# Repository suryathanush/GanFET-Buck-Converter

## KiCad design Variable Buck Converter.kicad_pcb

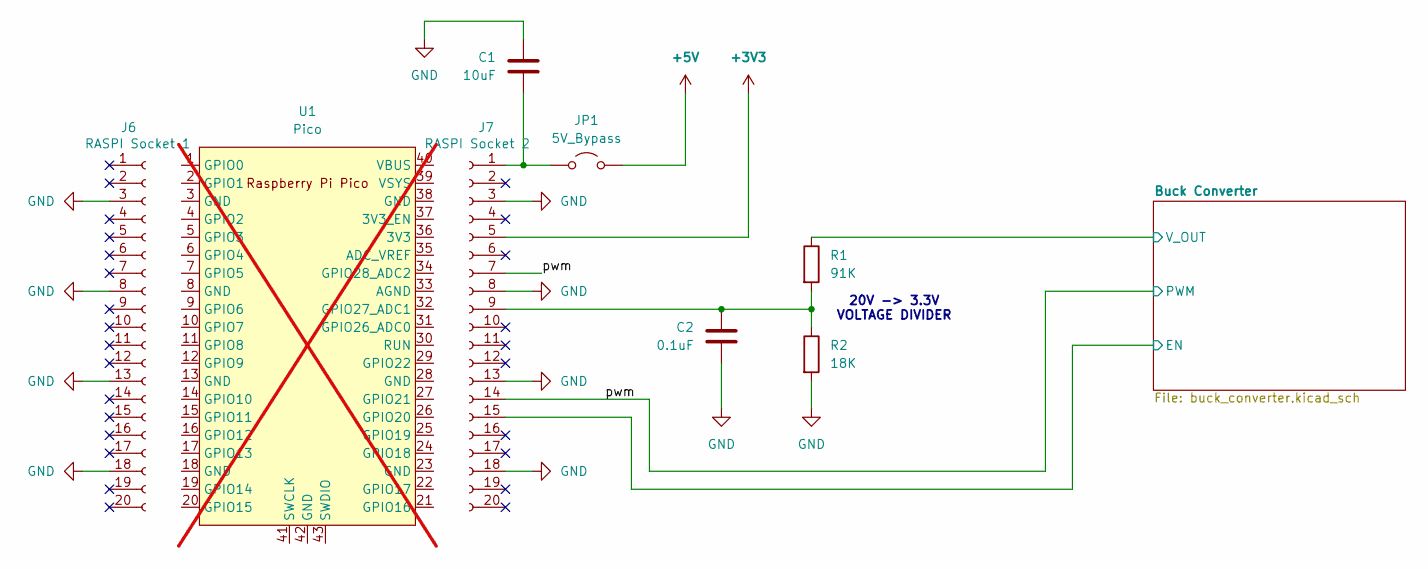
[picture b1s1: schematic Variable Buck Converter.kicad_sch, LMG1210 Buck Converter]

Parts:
C1: 10uF; C_0603_1608Metric; Manufacturer_Part_Number CL10A106MA8NRNC
C2: 0.1uF; C_0603_1608Metric; Manufacturer_Part_Number CL10B104JB8NNND
J6: RASPI Socket 1; PinSocket_1x20_P2.54mm_Vertical; Manufacturer_Part_Number PH1-20-UA
J7: RASPI Socket 2; PinSocket_1x20_P2.54mm_Vertical; Manufacturer_Part_Number PH1-20-UA
JP1: 5V_Bypass; PinHeader_1x02_P2.54mm_Vertical; Manufacturer_Part_Number HTSW-102-07-T-S
R1: 91K; R_0603_1608Metric; Manufacturer_Part_Number RT0603BRD0791KL
R2: 18K; R_0603_1608Metric; Manufacturer_Part_Number RT0603BRD0718KL
U1: Pico; RPi_Pico_SMD_TH; not fitted

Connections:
+3V3: J7.5; also elsewhere on the board
+5V: JP1.2 (B); also elsewhere on the board
/Buck Converter/EN: J7.15; also elsewhere on the board
/Buck Converter/V_OUT: R1.1; also elsewhere on the board
/pwm: J7.7, J7.14; also elsewhere on the board
GND: C1.1, C2.2, J6.3, J6.8, J6.13, J6.18, J7.3, J7.8, J7.13, J7.18, R2.2; also elsewhere on the board
unnamed: C1.2, J7.1, JP1.1 (A)
unnamed: C2.1, J7.9, R1.2, R2.1

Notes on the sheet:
20V -> 3.3V VOLTAGE DIVIDER

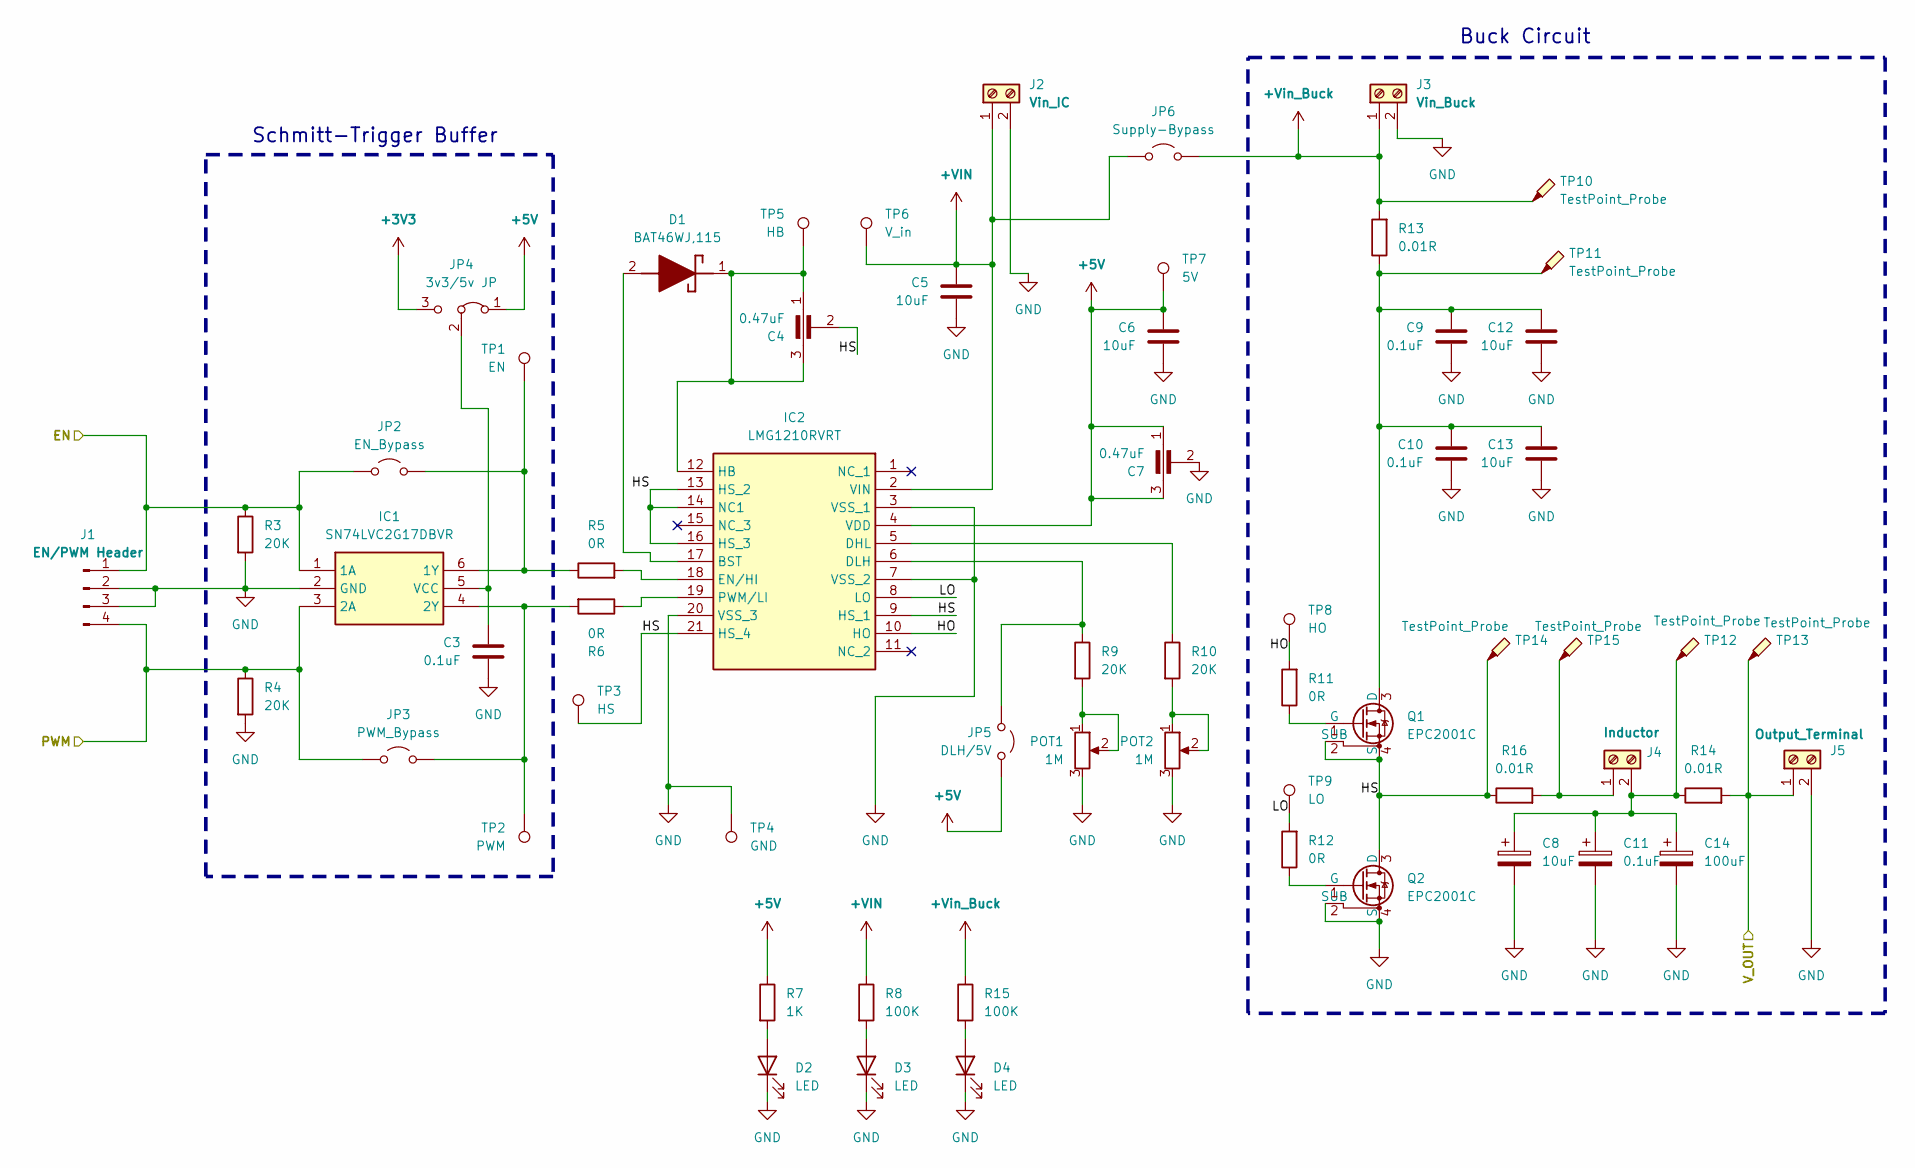
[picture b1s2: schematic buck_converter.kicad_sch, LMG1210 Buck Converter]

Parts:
C3, C9, C10, C11: 0.1uF; C_0603_1608Metric; Manufacturer_Part_Number CL10B104JB8NNND
C4, C7: 0.47uF; YFF18PW0J474MT0H0N; Manufacturer_Part_Number YFF18PW0J474MT0H0N
C5, C6, C8, C12, C13: 10uF; C_0603_1608Metric; Manufacturer_Part_Number CL10A106MA8NRNC
C14: 100uF; CP_Elec_6.3x5.9; Manufacturer_Part_Number 865080545012
D1: BAT46WJ,115; SODFL2512X80N; Manufacturer_Part_Number BAT46WJ,115; Mouser Part Number 771-BAT46WJ115
D2, D3, D4: LED; LED_0603_1608Metric; Manufacturer_Part_Number LTST-C190GKT
IC1: SN74LVC2G17DBVR; SOT95P280X145-6N; Manufacturer_Part_Number SN74LVC2G17DBVR; Mouser Part Number 595-SN74LVC2G17DBVR
IC2: LMG1210RVRT; Manufacturer_Part_Number LMG1210RVRT; Mouser Part Number 595-LMG1210RVRT
J1: EN/PWM Header; PinHeader_1x04_P2.54mm_Vertical; Manufacturer_Part_Number PH1-04-UA
J2: Vin_IC; TerminalBlock_Phoenix_MKDS-1,5-2_1x02_P5.00mm_Horizontal; Manufacturer_Part_Number 1548128
J3: Vin_Buck; TerminalBlock_Phoenix_MKDS-1,5-2_1x02_P5.00mm_Horizontal; Manufacturer_Part_Number 1548128
J4: Inductor; TerminalBlock_Phoenix_MKDS-1,5-2_1x02_P5.00mm_Horizontal; Manufacturer_Part_Number 1548128
J5: Output_Terminal; TerminalBlock_Phoenix_MKDS-1,5-2_1x02_P5.00mm_Horizontal; Manufacturer_Part_Number 1548128
JP2: EN_Bypass; PinHeader_1x02_P2.54mm_Vertical; Manufacturer_Part_Number HTSW-102-07-T-S
JP3: PWM_Bypass; PinHeader_1x02_P2.54mm_Vertical; Manufacturer_Part_Number HTSW-102-07-T-S
JP4: 3v3/5v JP; PinHeader_1x03_P2.54mm_Vertical; Manufacturer_Part_Number PH1-03-UA
JP5: DLH/5V; PinHeader_1x02_P2.54mm_Vertical; Manufacturer_Part_Number HTSW-102-07-T-S
JP6: Supply-Bypass; PinHeader_1x02_P2.54mm_Vertical; Manufacturer_Part_Number HTSW-102-07-T-S
POT1, POT2: 1M; Potentiometer_Bourns_3296W_Vertical; Manufacturer_Part_Number 3296W-1-105LF
Q1, Q2: EPC2001C; Manufacturer_Part_Number EPC2001C
R3, R4, R9, R10: 20K; R_0603_1608Metric; Manufacturer_Part_Number RT0603FRE0720KL
R5, R6, R11, R12: 0R; R_0603_1608Metric; Manufacturer_Part_Number RCG06030000Z0EA
R7: 1K; R_0603_1608Metric; Manufacturer_Part_Number RT0603FRE131KL
R8, R15: 100K; R_0603_1608Metric; Manufacturer_Part_Number RT0603FRE07100KL
R13, R14, R16: 0.01R; R_1206_3216Metric; Manufacturer_Part_Number PE1206DRM7W0R01L
TP1: EN; TestPoint_Loop_D2.60mm_Drill1.6mm_Beaded; Manufacturer_Part_Number 5278
TP2: PWM; TestPoint_Loop_D2.60mm_Drill1.6mm_Beaded; Manufacturer_Part_Number 5278
TP3: HS; TestPoint_Loop_D2.60mm_Drill1.6mm_Beaded; Manufacturer_Part_Number 5271
TP4: GND; TestPoint_Loop_D2.60mm_Drill1.6mm_Beaded; Manufacturer_Part_Number 5271
TP5: HB; TestPoint_Loop_D2.60mm_Drill1.6mm_Beaded; Manufacturer_Part_Number 5278
TP6: V_in; TestPoint_Loop_D2.60mm_Drill1.6mm_Beaded; Manufacturer_Part_Number 5270
TP7: 5V; TestPoint_Loop_D2.60mm_Drill1.6mm_Beaded; Manufacturer_Part_Number 5270
TP8: HO; TestPoint_Loop_D2.60mm_Drill1.6mm_Beaded; Manufacturer_Part_Number 5273
TP9: LO; TestPoint_Loop_D2.60mm_Drill1.6mm_Beaded; Manufacturer_Part_Number 5273
TP10, TP11: TestPoint_Probe; TestPoint_Loop_D2.60mm_Drill1.6mm_Beaded; Manufacturer_Part_Number 5270
TP12, TP13: TestPoint_Probe; TestPoint_Loop_D2.60mm_Drill1.6mm_Beaded; Manufacturer_Part_Number 5274
TP14, TP15: TestPoint_Probe; TestPoint_Loop_D2.60mm_Drill1.6mm_Beaded; Manufacturer_Part_Number 5277

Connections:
+3V3: JP4.3 (B); also elsewhere on the board
+5V: C6.1, C7.1, C7.3, IC2.4 (VDD), JP4.1 (A), JP5.1 (A), R7.1, TP7.1; also elsewhere on the board
+VIN: C5.1, IC2.2 (VIN), J2.1, JP6.1 (A), R8.1, TP6.1
+Vin_Buck: J3.1, JP6.2 (B), R13.2, R15.1, TP10.1
/Buck Converter/EN: IC1.1 (1A), J1.1, JP2.1 (A), R3.1; also elsewhere on the board
/Buck Converter/HO: IC2.10 (HO), R11.2, TP8.1
/Buck Converter/HS: C4.2, IC2.9 (HS_1), IC2.13 (HS_2), IC2.14 (NC1), IC2.16 (HS_3), IC2.21 (HS_4), Q1.2 (SUB), Q1.4 (S), Q1.6 (S), Q1.8 (S), Q1.10 (S), Q2.3 (D), Q2.5 (D), Q2.7 (D), Q2.9 (D), Q2.11 (D), R16.1, TP3.1, TP14.1
/Buck Converter/LO: IC2.8 (LO), R12.2, TP9.1
/Buck Converter/V_OUT: J5.1, R14.2, TP13.1; also elsewhere on the board
/pwm: IC1.3 (2A), J1.4, JP3.1 (A), R4.1; also elsewhere on the board
GND: C3.2, C5.2, C6.2, C7.2, C8.2, C9.2, C10.2, C11.2, C12.2, C13.2, C14.2, D2.1 (K), D3.1 (K), D4.1 (K), IC1.2 (GND), IC2.3 (VSS_1), IC2.7 (VSS_2), IC2.20 (VSS_3), J1.2, J1.3, J2.2, J3.2, J5.2, POT1.3, POT2.3, Q2.2 (SUB), Q2.4 (S), Q2.6 (S), Q2.8 (S), Q2.10 (S), R3.2, R4.2, TP4.1; also elsewhere on the board
unnamed: C9.1, C10.1, C12.1, C13.1, Q1.3 (D), Q1.5 (D), Q1.7 (D), Q1.9 (D), Q1.11 (D), R13.1, TP11.1
unnamed: D1.2 (A), IC2.17 (BST)
unnamed: C4.1, C4.3, D1.1 (K), IC2.12 (HB), TP5.1
unnamed: D2.2 (A), R7.2
unnamed: D3.2 (A), R8.2
unnamed: D4.2 (A), R15.2
unnamed: IC1.6 (1Y), JP2.2 (B), R5.1, TP1.1
unnamed: IC1.4 (2Y), JP3.2 (B), R6.2, TP2.1
unnamed: C3.1, IC1.5 (VCC), JP4.2 (C)
unnamed: IC2.5 (DHL), R10.1
unnamed: IC2.6 (DLH), JP5.2 (B), R9.1
unnamed: IC2.18 (EN/HI), R5.2
unnamed: IC2.19 (PWM/LI), R6.1
unnamed: J4.1, R16.2, TP15.1
unnamed: C8.1, C11.1, C14.1, J4.2, R14.1, TP12.1
unnamed: POT1.1, POT1.2, R9.2
unnamed: POT2.1, POT2.2, R10.2
unnamed: Q1.1 (G), R11.1
unnamed: Q2.1 (G), R12.1

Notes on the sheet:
Buck Circuit
Schmitt-Trigger Buffer

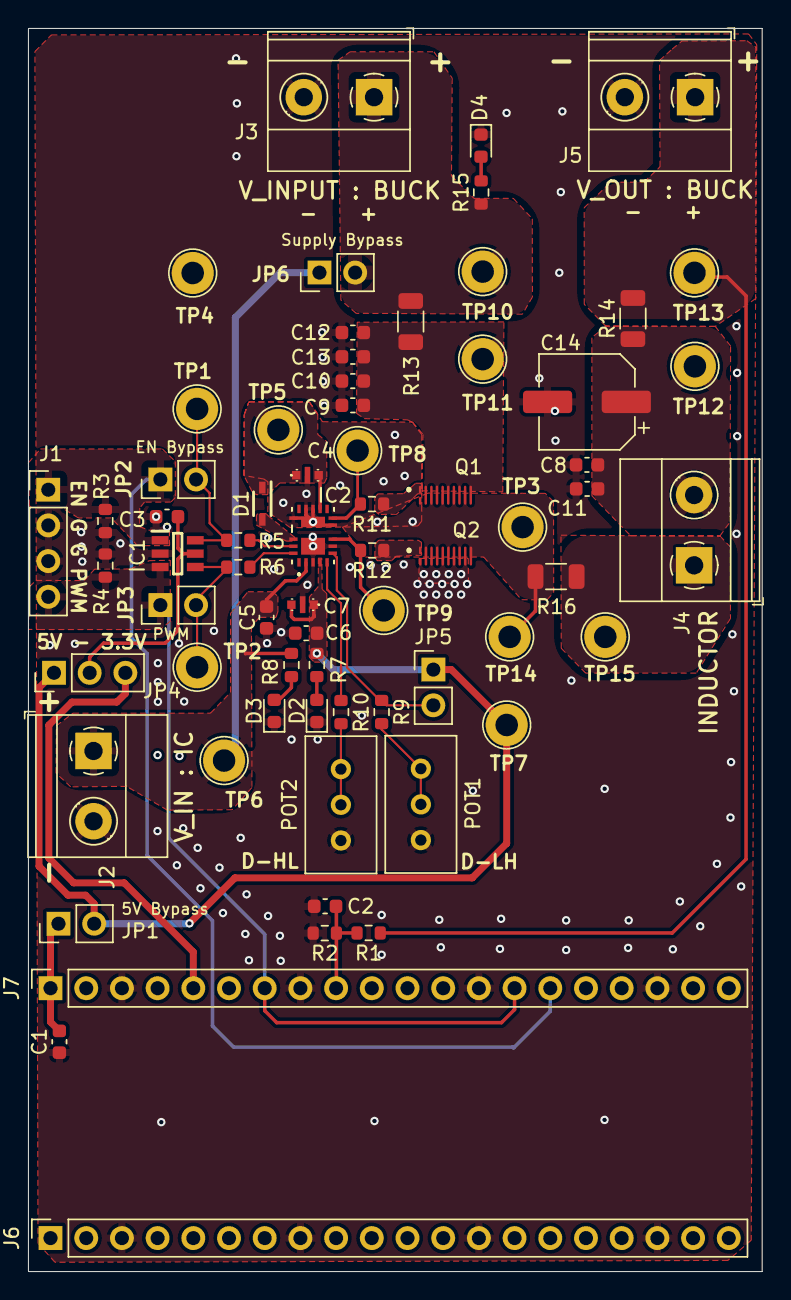
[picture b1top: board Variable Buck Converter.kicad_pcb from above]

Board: 4 copper layers, 52.2 x 88.4 mm, 68 parts (0 on the bottom side), 32 nets.

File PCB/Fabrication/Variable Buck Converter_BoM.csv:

Reference,Value,Footprint,Qty,Manufacturer_Part_Number
TP6,V_in,TestPoint:TestPoint_Loop_D2.60mm_Drill1.6mm_Beaded,1,5270
TP7,5V,TestPoint:TestPoint_Loop_D2.60mm_Drill1.6mm_Beaded,1,5270
"TP10,TP11",TestPoint_Probe,TestPoint:TestPoint_Loop_D2.60mm_Drill1.6mm_Beaded,2,5270
TP3,HS,TestPoint:TestPoint_Loop_D2.60mm_Drill1.6mm_Beaded,1,5271
TP4,GND,TestPoint:TestPoint_Loop_D2.60mm_Drill1.6mm_Beaded,1,5271
TP8,HO,TestPoint:TestPoint_Loop_D2.60mm_Drill1.6mm_Beaded,1,5273
TP9,LO,TestPoint:TestPoint_Loop_D2.60mm_Drill1.6mm_Beaded,1,5273
"TP12,TP13",TestPoint_Probe,TestPoint:TestPoint_Loop_D2.60mm_Drill1.6mm_Beaded,2,5274
"TP14,TP15",TestPoint_Probe,TestPoint:TestPoint_Loop_D2.60mm_Drill1.6mm_Beaded,2,5277
TP1,EN,TestPoint:TestPoint_Loop_D2.60mm_Drill1.6mm_Beaded,1,5278
TP2,PWM,TestPoint:TestPoint_Loop_D2.60mm_Drill1.6mm_Beaded,1,5278
TP5,HB,TestPoint:TestPoint_Loop_D2.60mm_Drill1.6mm_Beaded,1,5278
J2,Vin_IC,"TerminalBlock_Phoenix:TerminalBlock_Phoenix_MKDS-1,5-2_1x02_P5.00mm_Horizontal",1,1548128
J3,Vin_Buck,"TerminalBlock_Phoenix:TerminalBlock_Phoenix_MKDS-1,5-2_1x02_P5.00mm_Horizontal",1,1548128
J4,Inductor,"TerminalBlock_Phoenix:TerminalBlock_Phoenix_MKDS-1,5-2_1x02_P5.00mm_Horizontal",1,1548128
J5,Output_Terminal,"TerminalBlock_Phoenix:TerminalBlock_Phoenix_MKDS-1,5-2_1x02_P5.00mm_Horizontal",1,1548128
C14,100uF,Capacitor_SMD:CP_Elec_6.3x5.9,1,865080545012
"POT1,POT2",1M,Potentiometer_THT:Potentiometer_Bourns_3296W_Vertical,2,3296W-1-105LF
D1,"BAT46WJ,115","BAT46WJ,115:SODFL2512X80N",1,"BAT46WJ,115"
"C1,C5,C6,C8,C12,C13",10uF,Capacitor_SMD:C_0603_1608Metric,6,CL10A106MA8NRNC
"C2,C3,C9,C10,C11",0.1uF,Capacitor_SMD:C_0603_1608Metric,5,CL10B104JB8NNND
"Q1,Q2",EPC2001C,EPC2001C:EPC2001C,2,EPC2001C
JP1,5V_Bypass,Connector_PinHeader_2.54mm:PinHeader_1x02_P2.54mm_Vertical,1,HTSW-102-07-T-S
JP2,EN_Bypass,Connector_PinHeader_2.54mm:PinHeader_1x02_P2.54mm_Vertical,1,HTSW-102-07-T-S
JP3,PWM_Bypass,Connector_PinHeader_2.54mm:PinHeader_1x02_P2.54mm_Vertical,1,HTSW-102-07-T-S
JP5,DLH/5V,Connector_PinHeader_2.54mm:PinHeader_1x02_P2.54mm_Vertical,1,HTSW-102-07-T-S
JP6,Supply-Bypass,Connector_PinHeader_2.54mm:PinHeader_1x02_P2.54mm_Vertical,1,HTSW-102-07-T-S
IC2,LMG1210RVRT,LMG1210:LMG1210RVRT,1,LMG1210RVRT
"D2,D3,D4",LED,LED_SMD:LED_0603_1608Metric,3,LTST-C190GKT
"R13,R14,R16",0.01R,Resistor_SMD:R_1206_3216Metric,3,PE1206DRM7W0R01L
JP4,3v3/5v JP,Connector_PinHeader_2.54mm:PinHeader_1x03_P2.54mm_Vertical,1,PH1-03-UA
J1,EN/PWM Header,Connector_PinHeader_2.54mm:PinHeader_1x04_P2.54mm_Vertical,1,PH1-04-UA
J6,RASPI Socket 1,Connector_PinSocket_2.54mm:PinSocket_1x20_P2.54mm_Vertical,1,PH1-20-UA
J7,RASPI Socket 2,Connector_PinSocket_2.54mm:PinSocket_1x20_P2.54mm_Vertical,1,PH1-20-UA
"R5,R6,R11,R12",0R,Resistor_SMD:R_0603_1608Metric,4,RCG06030000Z0EA
R2,18K,Resistor_SMD:R_0603_1608Metric,1,RT0603BRD0718KL
R1,91K,Resistor_SMD:R_0603_1608Metric,1,RT0603BRD0791KL
R7,1K,Resistor_SMD:R_0603_1608Metric,1,RT0603FRE131KL
"R3,R4,R9,R10",20K,Resistor_SMD:R_0603_1608Metric,4,RT0603FRE0720KL
"R8,R15",100K,Resistor_SMD:R_0603_1608Metric,2,RT0603FRE07100KL
IC1,SN74LVC2G17DBVR,SN74LVC2G17DBVR:SOT95P280X145-6N,1,SN74LVC2G17DBVR
"C4,C7",0.47uF,YFF18PW0J474M:YFF18PW0J474MT0H0N,2,YFF18PW0J474MT0H0N

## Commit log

2025-04-16 v1.1.0 design
2025-04-21 v1.1.0 Gerber
2025-04-21 v1.1.0 SCH Pdf
2025-04-21 C14 change, BoM and CPL
2025-05-31 firmware doc
2025-05-31 readme
